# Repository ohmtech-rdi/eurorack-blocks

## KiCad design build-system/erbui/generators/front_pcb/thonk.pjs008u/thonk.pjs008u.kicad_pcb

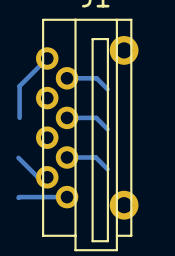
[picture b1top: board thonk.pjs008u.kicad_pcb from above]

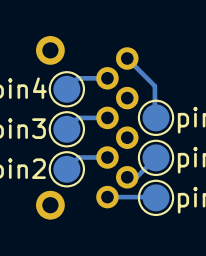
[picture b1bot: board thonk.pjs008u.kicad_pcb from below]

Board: 2 copper layers, 7 parts (6 on the bottom side), 7 nets.

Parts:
J1: Micro_SD_Card; PJS008U
TP1, TP2, TP3, TP4, TP5, TP6: TestPoint; TestPoint_Pad_D1.5mm

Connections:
GND: J1.6, J1.9
unnamed: J1.1, TP1.1
unnamed: J1.2, TP2.1
unnamed: J1.3, TP3.1
unnamed: J1.5, TP4.1
unnamed: J1.7, TP5.1
unnamed: J1.8, TP6.1
